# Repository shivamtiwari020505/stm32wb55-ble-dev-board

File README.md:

# stm32wb55-ble-dev-board

> A compact, 4-layer prototype Input/Output board built around the **STM32WB55CEU6** — a dual-core ARM wireless SoC with Bluetooth 5.0 and IEEE 802.15.4 support.

---

## 📌 Overview

The **stm32wb55-ble-dev-board** is a feature-rich embedded development platform designed for IoT, wireless sensing, and industrial control applications. It integrates a high-performance wireless microcontroller with USB-C connectivity, RS232 PC interfacing, RF front-end matching, and a comprehensive set of expansion headers — all on a compact, professional-grade 4-layer red PCB.

---

## 🖼️ Board Preview

| PCB Layout | Circuit Schematic |
|:---:|:---:|
|  |  

---

## ✨ Features

- **Dual-Core Wireless MCU** — STM32WB55CEU6 (ARM Cortex-M4 @ 64 MHz + ARM Cortex-M0+ radio core)
- **Bluetooth 5.0 / IEEE 802.15.4** — Zigbee, Thread, OpenThread ready
- **2.4 GHz RF Front-End** — Discrete LC matching network + U.F.L. coaxial antenna connector
- **USB-C Interface** — USB 2.0 Full Speed with ESD protection (USBLC6-2SC6)
- **RS232 PC Interface** — MAX3232 level converter + DB9 connector for legacy serial port compatibility
- **Clean Power Architecture** — MIC5365-3.3YD5 LDO (+5V → +3.3V) with distributed decoupling
- **SWD Debug Interface** — Tag-Connect header (SWDIO, SWDCLK, SWO, NRST)
- **DFU Bootloader** — BOOT0 push-button for USB firmware flashing
- **Expansion Headers** — UART, LPUART, I2C
- **Dual Crystal Oscillators** — 32 MHz HSE (RF) + 32.768 kHz LSE (RTC)
- **4-Layer Red PCB** — M3 mounting holes × 4, Fiducial markers × 3

---

## 🔧 Hardware Specifications

| Parameter | Specification |
|-----------|--------------|
| Microcontroller | STM32WB55CEU6 (Cortex-M4 @ 64 MHz + Cortex-M0+) |
| Flash / SRAM | 512 KB Flash / 256 KB SRAM |
| Wireless Protocol | Bluetooth 5.0, IEEE 802.15.4 (Zigbee, Thread) |
| RF Frequency | 2.400 – 2.500 GHz |
| RF Connector | U.F.L. Coaxial |
| Power Input | +5V via USB-C or external header |
| Operating Voltage | +3.3V (MIC5365-3.3YD5 LDO) |
| USB Interface | USB-C 2.0 Full Speed + ESD (USBLC6-2SC6) |
| Serial Interfaces | UART, LPUART, I2C, SWD, RS232 (MAX3232) |
| PC Serial Port | DB9 connector (RS232 ±12V) |
| Debug Interface | SWD Tag-Connect + NRST |
| HSE Crystal | 32 MHz |
| LSE Crystal | 32.768 kHz |
| Boot Mode | BOOT0 push-button switch |
| Mounting Holes | M3 × 4 (H1–H4) |
| Fiducial Markers | FM1, FM2, FM3 |
| PCB | Red, 4-Layer |
| Form Factor | ~80 mm × 35 mm |

---

## 📁 Repository Structure

```
stm32wb55-ble-dev-board/
├── Manufacturing/                          # Gerber files & fabrication outputs
├── Version1_IO_PCBFootprints.pretty/       # Custom KiCad footprint library
├── stm32wb55-ble-dev-board.kicad_pcb       # PCB layout file
├── stm32wb55-ble-dev-board.kicad_sch       # Schematic file
├── stm32wb55-ble-dev-board.kicad_pro       # KiCad project file
├── stm32wb55-ble-dev-board.kicad_prl       # PCB local settings
├── Version1_IO_SchematicSymbol.kicad_sym   # Custom schematic symbol library
├── 530480410.stp                           # 3D model (STEP)
├── DLF162500LT-5028A1--3DModel-STEP.step   # 3D model — RF filter
├── QFN127P600-8N.step                      # 3D model — QFN package
├── fp-lib-table                            # KiCad footprint library table
├── sym-lib-table                           # KiCad symbol library table
├── docs/
│   ├── pcb_layout.jpg                      # PCB layout image
│   └── schematic.jpg                       # Schematic image
└── README.md
```

---

## 🚀 Getting Started

### Prerequisites

- [STM32CubeIDE](https://www.st.com/en/development-tools/stm32cubeide.html) or [STM32CubeWB](https://www.st.com/en/embedded-software/stm32cubewb.html)
- [STM32CubeProgrammer](https://www.st.com/en/development-tools/stm32cubeprog.html) for flashing
- Tag-Connect TC2050 cable for SWD debug
- USB-C cable for power and USB DFU flashing

### Flashing via SWD

1. Connect a Tag-Connect TC2050 cable to the SWD header on the board.
2. Open STM32CubeIDE or STM32CubeProgrammer.
3. Select **STM32WB55CEU6** as the target device.
4. Flash your `.elf` or `.hex` firmware file.

### Flashing via USB DFU (Bootloader)

1. Hold the **BOOT0** button while powering the board via USB-C.
2. The MCU will enumerate as a DFU device on your PC.
3. Use STM32CubeProgrammer or `dfu-util` to flash:

```bash
dfu-util -a 0 -s 0x08000000:leave -D firmware.bin
```

### RS232 / PC Serial Interface

Connect a DB9 serial cable between the board and your PC (or use a USB-to-RS232 adapter). The MAX3232 handles level conversion automatically. Default UART settings:

```
Baud Rate : 115200
Data Bits : 8
Parity    : None
Stop Bits : 1
Flow Ctrl : None
```

---

## 📡 RF & Antenna

The RF front-end uses a discrete LC matching network and low-pass filter (DLC1625D-S0Z8A5) tuned for the 2.4–2.5 GHz band, feeding into a **U.F.L. coaxial connector**. Connect an external 2.4 GHz antenna (via U.F.L. or SMA adapter) before powering the RF subsystem.

> ⚠️ **Do not operate the RF transmitter without an antenna connected.** This may damage the RF front-end.

---

## 🔌 Pinout & Connectors

| Connector / Header | Signal(s) | Description |
|--------------------|-----------|-------------|
| USB-C (J1) | VBUS, D+, D−, CC1, CC2 | USB 2.0 Full Speed + Power |
| SWD Tag-Connect | SWDIO, SWDCLK, SWO, NRST, GND, 3V3 | Debug & Programming |
| UART Header | UART_TX, UART_RX, GND | General-purpose UART |
| LPUART Header | LPUART_TX, LPUART_RX, GND | Low-power UART |
| I2C Header | I2C_SCL, I2C_SDA, GND, 3V3 | I2C expansion |
| DB9 (J5) | RS232 TX, RX | PC serial port |
| RF (J1) | RF_ANT | U.F.L. coaxial antenna |
| BOOT0 (SW1) | BOOT0 | DFU bootloader trigger |

---

## 📐 PCB Stack-up

| Layer | Function |
|-------|----------|
| L1 (Top) | Signal + Components |
| L2 | Ground Plane |
| L3 | Power Plane (+3.3V) |
| L4 (Bottom) | Signal |

---

## 🤝 Contributing

Pull requests are welcome! For major changes, please open an issue first to discuss what you would like to change.

---

## 📬 Contact

For questions or collaboration, open an issue on this repository.

---

*Designed with STM32WB55CEU6 · 4-Layer PCB · Bluetooth 5.0 · IEEE 802.15.4*

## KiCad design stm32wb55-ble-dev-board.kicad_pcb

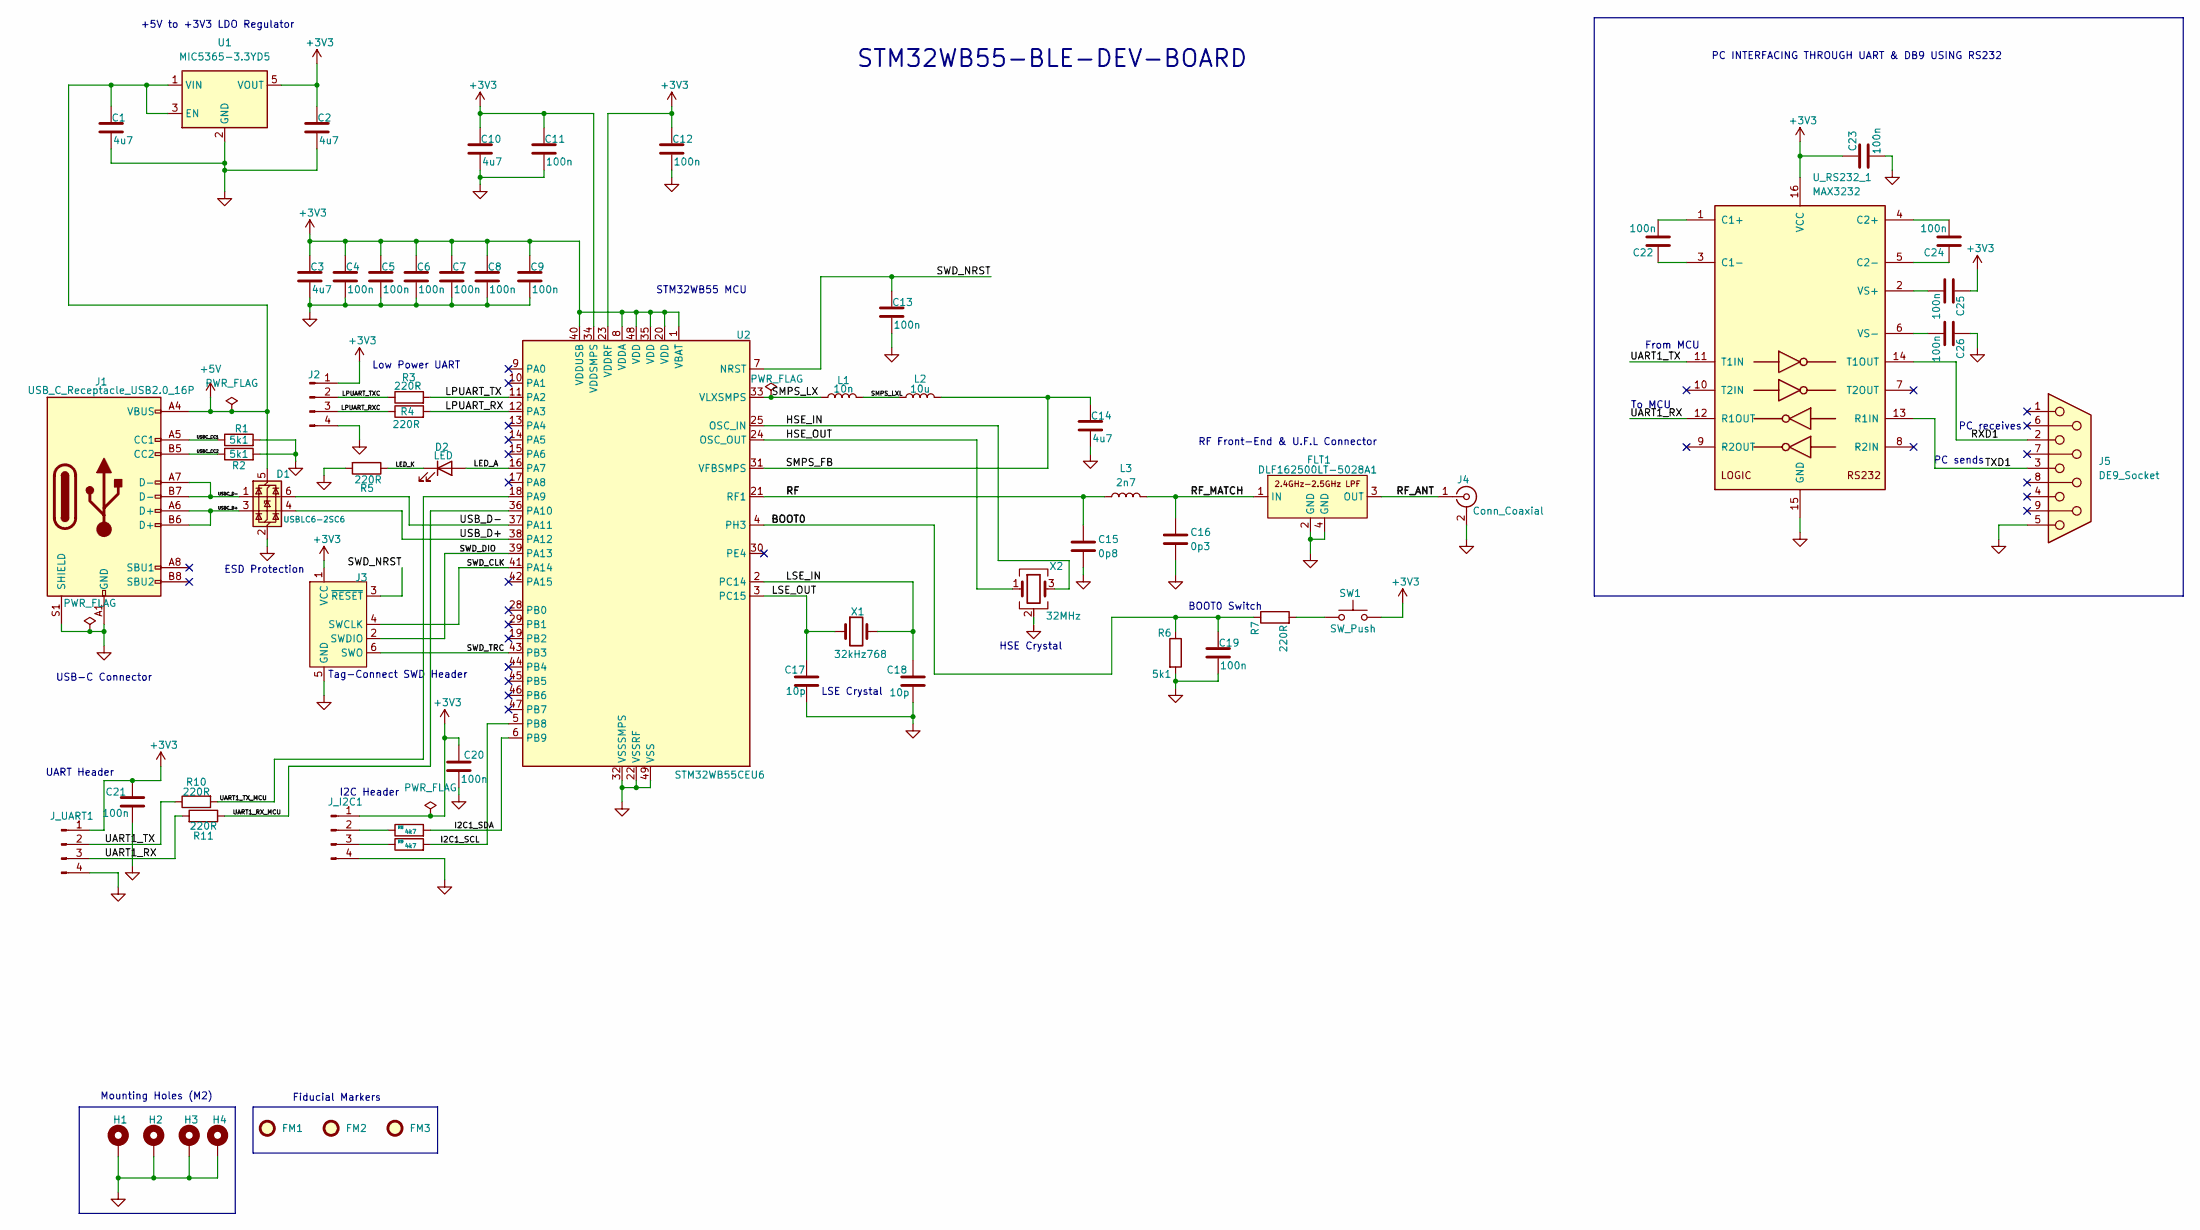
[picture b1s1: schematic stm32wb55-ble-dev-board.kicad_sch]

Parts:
C1, C2, C3, C10, C14: 4u7; C_0603_1608Metric
C4, C5, C6, C7, C8, C9, C11, C12, C13, C19, C20, C21, C22, C23, C24, C25, C26: 100n; C_0402_1005Metric
C15: 0p8; C_0402_1005Metric
C16: 0p3; C_0402_1005Metric
C17, C18: 10p; C_0402_1005Metric
D1: USBLC6-2SC6; SOT-23-6
D2: LED; LED_0402_1005Metric
FLT1: DLF162500LT-5028A1
FM1, FM2, FM3: Fiducial; Fiducial_1mm_Mask2mm
H1, H2, H3, H4: MountingHole_Pad; MountingHole_2.2mm_M2_Pad_Via
J1: USB_C_Receptacle_USB2.0_16P; USB_C_Receptacle_GCT_USB4105-xx-A_16P_TopMnt_Horizontal
J2: Conn_01x04_Pin; Molex_PicoBlade_53048-0410_1x04_P1.25mm_Horizontal
J3: Conn_ARM_SWD_TagConnect_TC2030; Tag-Connect_TC2030-IDC-FP_2x03_P1.27mm_Vertical
J4: Conn_Coaxial; U.FL_Hirose_U.FL-R-SMT-1_Vertical
J5: DE9_Socket; DSUB-9_Socket_Horizontal_P2.77x2.84mm_EdgePinOffset4.94mm_H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
J_I2C1: Conn_01x04_Pin; PinHeader_1x04_P2.54mm_Vertical
J_UART1: Conn_01x04_Pin; PinHeader_1x04_P2.54mm_Vertical
L1: 10n; L_0402_1005Metric
L2: 10u; L_0805_2012Metric
L3: 2n7; L_0402_1005Metric
R1, R2, R6: 5k1; R_0402_1005Metric
R3, R4, R5, R7, R10, R11: 220R; R_0402_1005Metric
R8, R9: 4k7; R_0402_1005Metric
SW1: SW_Push; SW_SPST_CK_RS282G05A3
U1: MIC5365-3.3YD5; TSOT-23-5
U2: STM32WB55CEU6; QFN-48-1EP_7x7mm_P0.5mm_EP5.6x5.6mm
U_RS232_1: MAX3232; SOIC-16_3.9x9.9mm_P1.27mm
X1: 32kHz768; Crystal_SMD_2012-2Pin_2.0x1.2mm
X2: 32MHz; Crystal_SMD_2016-4Pin_2.0x1.6mm

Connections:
+3V3: C2.1, C3.1, C4.1, C5.1, C6.1, C7.1, C8.1, C9.1, C10.1, C11.1, C12.1, C20.1, C21.1, C23.1, C25.1, J2.1, J3.1 (VCC), J_I2C1.1, J_UART1.1, SW1.2, U1.5 (VOUT), U2.1 (VBAT), U2.8 (VDDA), U2.20 (VDD), U2.23 (VDDRF), U2.34 (VDDSMPS), U2.35 (VDD), U2.40 (VDDUSB), U2.48 (VDD), U_RS232_1.16 (VCC)
+5V: C1.1, D1.5 (VBUS), J1.A4 (VBUS), J1.A9 (VBUS), J1.B4 (VBUS), J1.B9 (VBUS), U1.1 (VIN), U1.3 (EN)
/BOOT0: C19.1, R6.1, R7.1, U2.4 (PH3)
/HSE_IN: U2.25 (OSC_IN), X2.3
/HSE_OUT: U2.24 (OSC_OUT), X2.1
/I2C1_SCL: R9.2, U2.5 (PB8)
/I2C1_SDA: R8.2, U2.6 (PB9)
/LED_A: D2.2 (A), U2.16 (PA7)
/LED_K: D2.1 (K), R5.1
/LPUART_RX: R4.2, U2.12 (PA3)
/LPUART_RXC: J2.3, R4.1
/LPUART_TX: R3.2, U2.11 (PA2)
/LPUART_TXC: J2.2, R3.1
/LSE_IN: C18.1, U2.2 (PC14), X1.2
/LSE_OUT: C17.1, U2.3 (PC15), X1.1
/RF: C15.1, L3.1, U2.21 (RF1)
/RF_ANT: FLT1.3 (OUT), J4.1 (In)
/RF_MATCH: C16.1, FLT1.1 (IN), L3.2
/RXD1: J5.2, U_RS232_1.14 (T1OUT)
/SMPS_FB: C14.1, L2.2, U2.31 (VFBSMPS)
/SMPS_LX: L1.1, U2.33 (VLXSMPS)
/SMPS_LXL: L1.2, L2.1
/SWD_CLK: J3.4 (SWCLK), U2.41 (PA14)
/SWD_DIO: J3.2 (SWDIO), U2.39 (PA13)
/SWD_NRST: C13.1, J3.3 (~RESET), U2.7 (NRST)
/SWD_TRC: J3.6 (SWO), U2.43 (PB3)
/TXD1: J5.3, U_RS232_1.13 (R1IN)
/UART1_RX: J_UART1.3, R11.2, U_RS232_1.12 (R1OUT)
/UART1_RX_MCU: R11.1, U2.36 (PA10)
/UART1_TX: J_UART1.2, R10.1, U_RS232_1.11 (T1IN)
/UART1_TX_MCU: R10.2, U2.18 (PA9)
/USBC_CC1: J1.A5 (CC1), R1.1
/USBC_CC2: J1.B5 (CC2), R2.1
/USBC_D+: D1.3 (I/O2), J1.A6 (D+), J1.B6 (D+)
/USBC_D-: D1.1 (I/O1), J1.A7 (D-), J1.B7 (D-)
/USB_D+: D1.4 (I/O2), U2.38 (PA12)
/USB_D-: D1.6 (I/O1), U2.37 (PA11)
GND: C1.2, C2.2, C3.2, C4.2, C5.2, C6.2, C7.2, C8.2, C9.2, C10.2, C11.2, C12.2, C13.2, C14.2, C15.2, C16.2, C17.2, C18.2, C19.2, C20.2, C21.2, C23.2, C26.1, D1.2 (GND), FLT1.2 (GND), FLT1.4 (GND), H1.1, H2.1, H3.1, H4.1, J1.A1 (GND), J1.A12 (GND), J1.B1 (GND), J1.B12 (GND), J1.S1 (SHIELD), J2.4, J3.5 (GND), J4.2 (Ext), J5.5, J_I2C1.4, J_UART1.4, R1.2, R2.2, R5.2, R6.2, U1.2 (GND), U2.22 (VSSRF), U2.32 (VSSSMPS), U2.49 (VSS), U_RS232_1.15 (GND), X2.2 (G), X2.4 (G)
unnamed: J_I2C1.2, R8.1
unnamed: J_I2C1.3, R9.1
unnamed: R7.2, SW1.1
unnamed: C22.2, U_RS232_1.1 (C1+)
unnamed: C22.1, U_RS232_1.3 (C1-)
unnamed: C24.2, U_RS232_1.4 (C2+)
unnamed: C24.1, U_RS232_1.5 (C2-)
unnamed: C25.2, U_RS232_1.2 (VS+)
unnamed: C26.2, U_RS232_1.6 (VS-)

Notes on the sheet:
STM32WB55 MCU
PC sends
USB-C Connector
From MCU
PC INTERFACING THROUGH UART & DB9 USING RS232
Mounting Holes (M2)
To MCU
ESD Protection
HSE Crystal
LSE Crystal
PC receives
I2C Header
BOOT0 Switch
Low Power UART
Fiducial Markers
UART Header
Tag-Connect SWD Header
RF Front-End & U.F.L Connector
STM32WB55-BLE-DEV-BOARD
+5V to +3V3 LDO Regulator

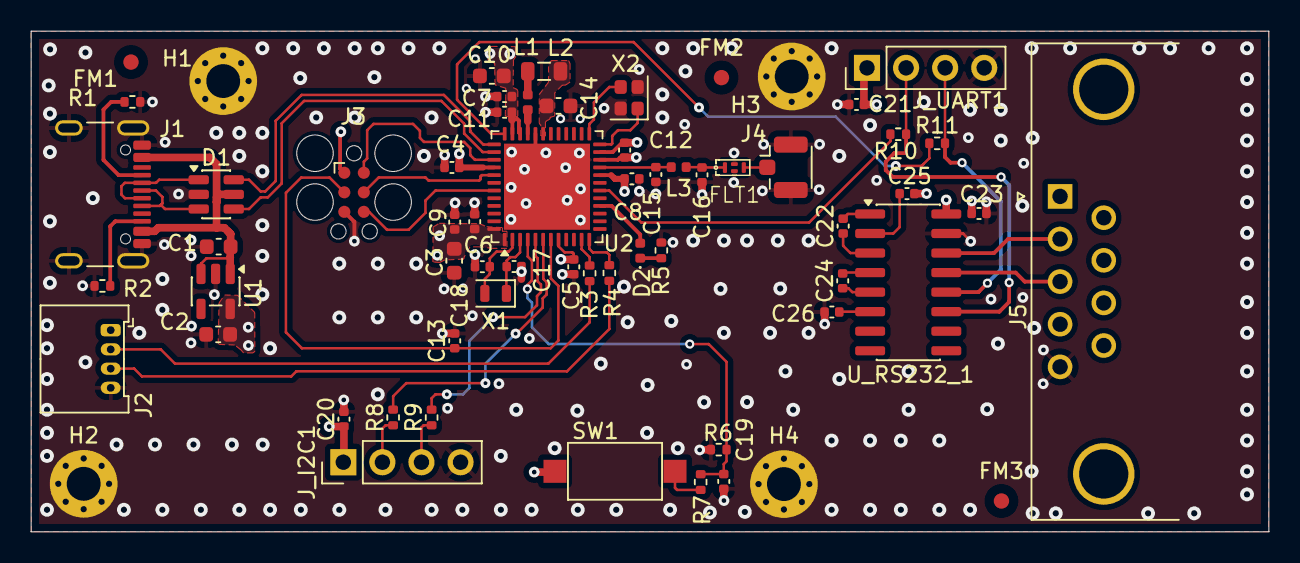
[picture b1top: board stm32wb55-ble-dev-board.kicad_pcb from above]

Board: 4 copper layers, 80.5 x 32.5 mm, 63 parts (0 on the bottom side), 47 nets.

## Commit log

2026-04-20 Add files via upload
    Initial commit: Added custom STM32WB55 schematic, PCB layout, 3D models, and manufacturing gerbers
2026-04-22 Add MIT License to the project
2026-04-22 Enhance README with detailed board information
    Expanded the README to include detailed features, specifications, and usage instructions for the STM32WB55 development board.
2026-05-04 Rename PCB_SHEMATIC.jpg to PCB_SCHEMATIC.jpg
